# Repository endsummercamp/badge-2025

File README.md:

# badge-2025

Repository containing the schematics for the flex PCB badge distributed at ESC{21}.

The schematics are licensed under the CERN OHL S v2 license.

The badge has been designed by [Jacopo Franco](https://www.jacopofranco.com/), that we thank for the effort in making this literal show of force a reality ;)

Special thanks to [Kezi](https://github.com/Kezii), [Kowalski](https://github.com/kowalski7cc), [K3lite](https://github.com/k3lite) & [Baobots](https://github.com/baobots) for the efforts spent into debugging & flashing all of them during the camp.

And for going the extra mile and designing a custom case that solves many assembly issues, a very felt thanks to [k0bld](https://github.com/k0bld).

<video src="https://github.com/user-attachments/assets/acb0492f-e134-4207-b74a-9145ce9de10b"
       autoplay
       loop
       muted
       playsinline
       width="600">
  Your browser does not support the video tag.
</video>

---

# Badge Instructions

## Assembly

* The badge must be folded into position.
* To keep it fixed, we recommend using **UV glue**, **superglue**, or **thin double-sided tape**.
* **Do not solder directly** onto the PET substrate — this is very challenging, even with bismuth low-temperature solder.

## Flashing
**USB communication is not supported** — the port is for charging only.
To flash the badge the first time, make use of the UART and the power pins as below.

### USB-C Connector

* The USB-C must also be folded.
* Align the tab with the solid line located after the resistors.
* With the **copper contacts facing outward**, insert the connector into a male USB Type-C cable.

---

## Charging
* There are no LEDs to indicate charging progress. The charger is however guaranteed to fully charge the battery in 2.5h. The battery is fully protected and the charger has multiple overcurrent, overvoltage and temperature protections. It can trickle-charge.
* Battery life is approximately 4h with the "All sides music" profile and the WiFi radio at 8.5dBm.
* An **interrupt pin** connected to the charger will change state during charging. You will have to implement it yourself.

---

## Firmware

* The badge ships with the **WLED firmware** by default.
* * Firmware updates can be done via **WLED OTA** or the **Serial pads**.
* To connect:

  1. Connect to the Wi-Fi network:

     ```text
     SSID: wled-ap  
     Password: wled1234
     ```
  2. Open the address in your browser:

     ```text
     4.3.2.1
     ```

---

## Pinout

```text
Charger status:       GPIO 10
Battery voltage:      Analog GPIO 3 (divider only enabled when LED MOSFET is ON)
LEDs MOSFET:          GPIO 4
LED data:             GPIO 8
I²C SDA:              GPIO 7
I²C SCL:              GPIO 6
Touch button 1:       GPIO 0
Touch button 2:       GPIO 1
```

---

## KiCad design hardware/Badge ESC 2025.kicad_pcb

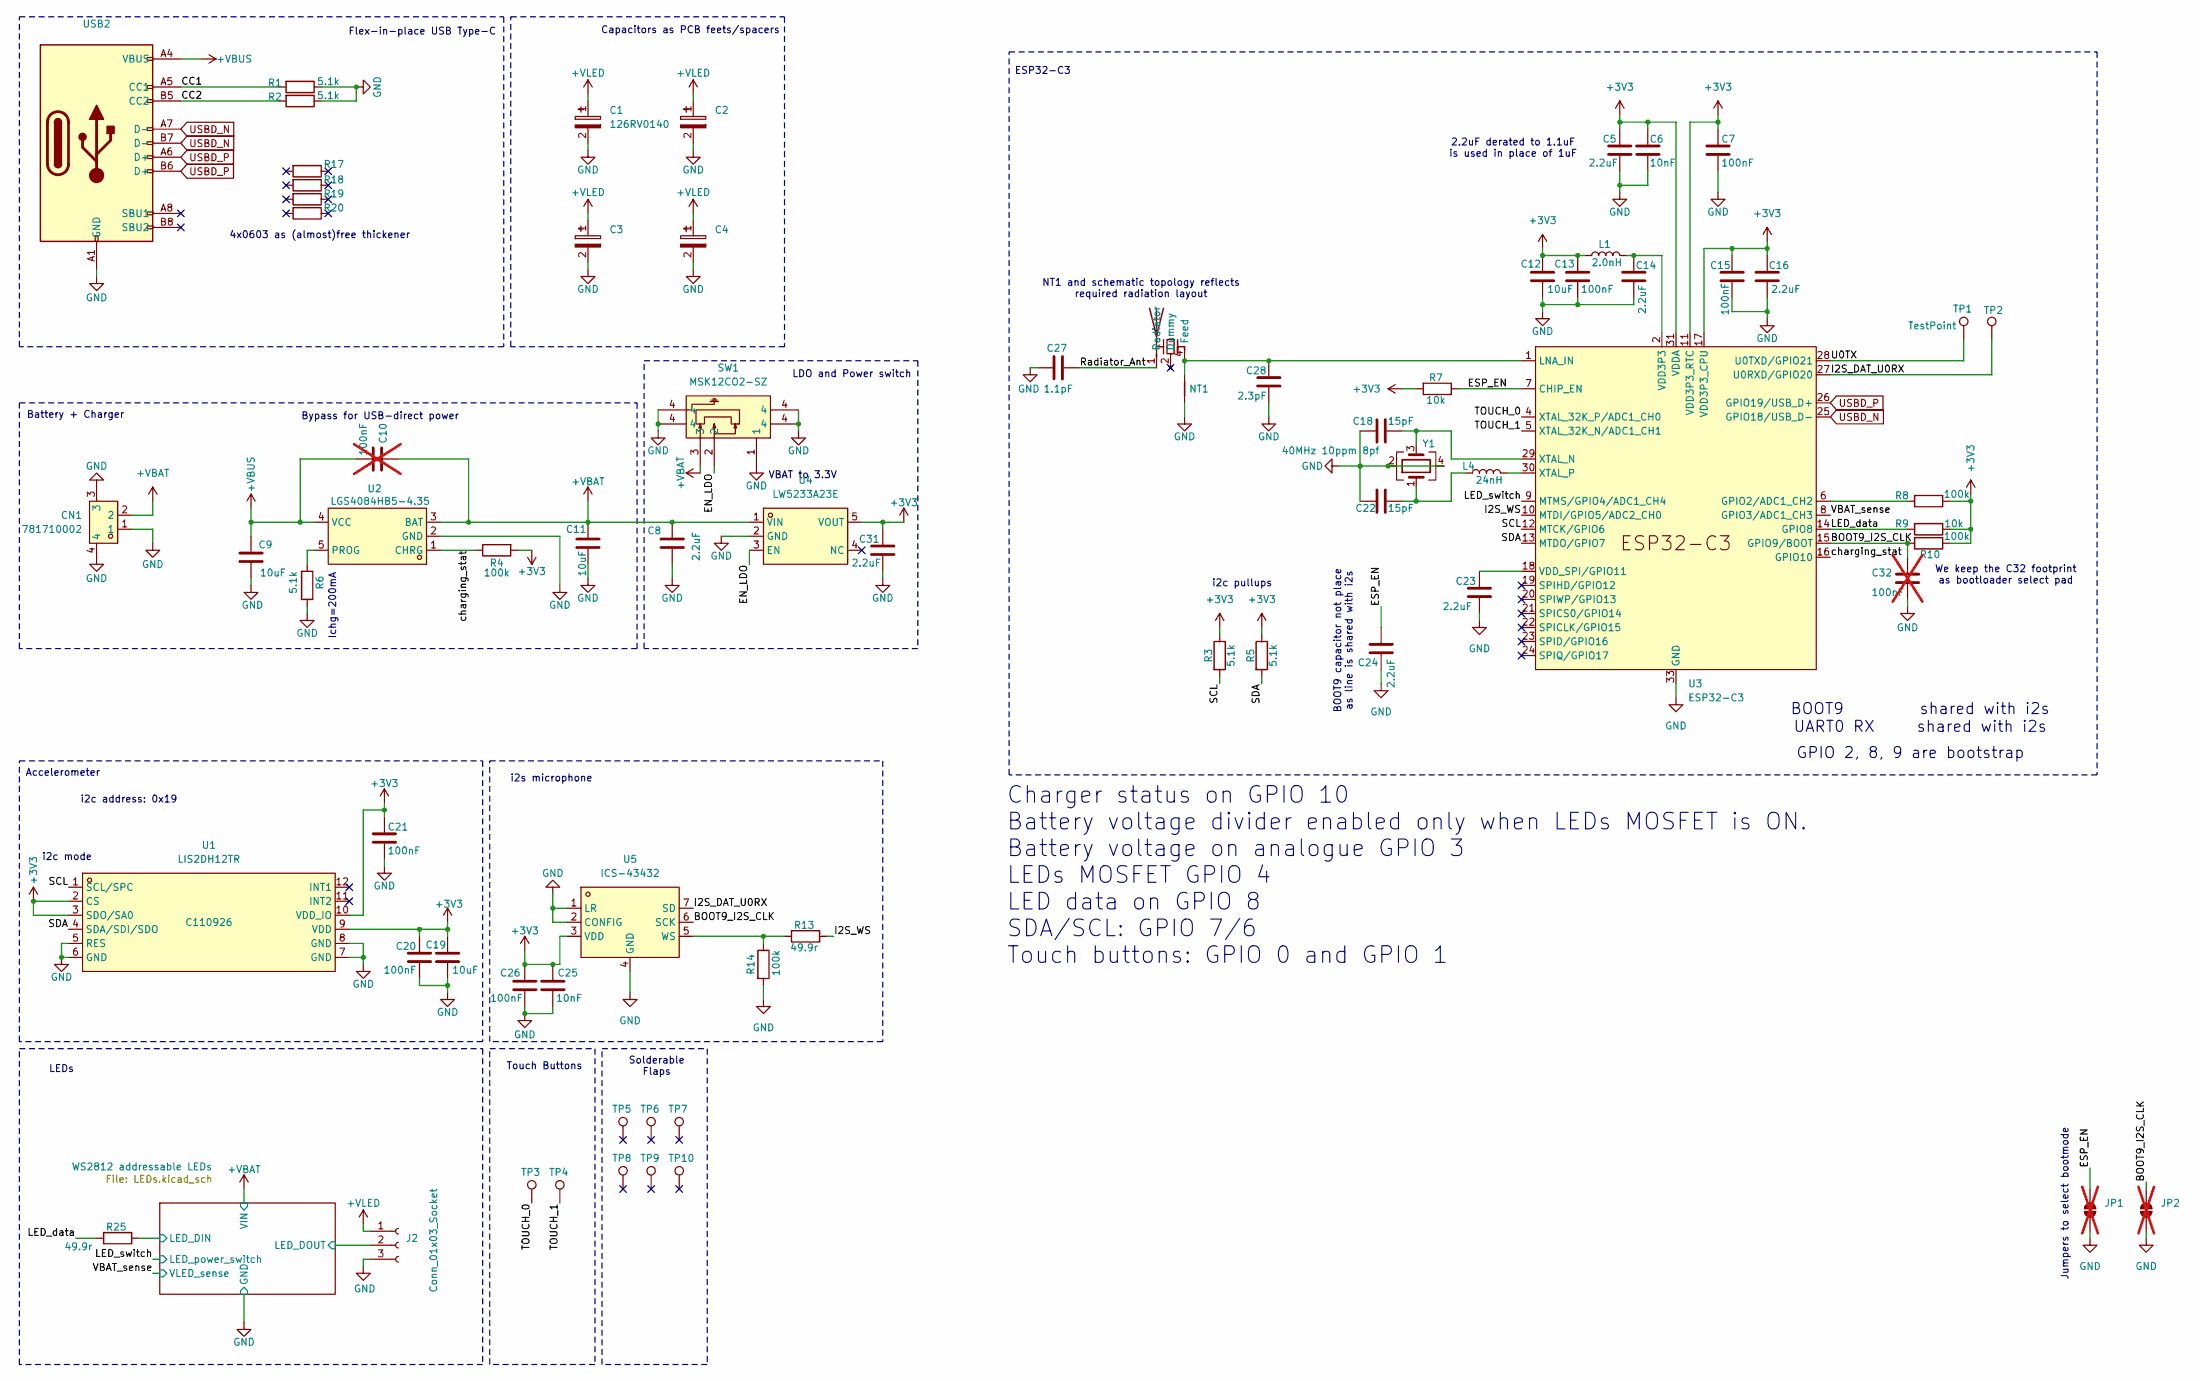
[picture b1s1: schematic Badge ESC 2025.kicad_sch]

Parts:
ANT2: ANT016008LCS2442MA; ANT-SMD_6P-L1.6-W0.8-P1.20-1; LCSC C76585
C1, C2, C3, C4: 126RV0140; CAP-SMD_BD4.0-L4.3-W4.3-LS5.1-FD; LCSC C7461271
C5, C8, C14, C16, C23, C24, C31: 2.2uF; C_0402_1005Metric; LCSC C12530
C6, C25: 10nF; C_0402_1005Metric; LCSC C15195
C7, C13, C15, C20, C21, C26: 100nF; C_0402_1005Metric; LCSC C1525
C9, C11, C12, C19: 10uF; C_0603_1608Metric; LCSC C19702
C10, C32: 100nF; C_0402_1005Metric; LCSC C1525; not fitted
C18, C22: 15pF; C_0402_1005Metric; LCSC C1548
C27: 1.1pF; C_0402_1005Metric; LCSC C88920
C28: 2.3pF; C_0402_1005Metric; LCSC C2190124
CN1: 781710002; CONN-SMD_2P-P1.20_781710002; LCSC Part C505023
J2: Conn_01x03_Socket; SolderJumper-3_P1.3mm_Open_RoundedPad1.0x1.5mm_NumberLabels
JP1, JP2: SolderJumper_2_Open; SolderJumper-2_P1.3mm_Open_Pad0.5x0.5mm; not fitted
L1: 2.0nH; L_0402_1005Metric; LCSC C76769
L4: 24nH; L_0402_1005Metric; LCSC C404641
NT1: NetTie_2; net_tie_2pins_0.2
R1, R2, R3, R5, R6: 5.1k; R_0402_1005Metric; LCSC C25905
R4, R8, R10, R14: 100k; R_0402_1005Metric; LCSC C25741
R7, R9: 10k; R_0402_1005Metric; LCSC C25744
R13, R17, R18, R19, R20, R25: 49.9r; R_0603_1608Metric; LCSC C23185
SW1: MSK12CO2-SZ; SW-TH_MSK12C02; LCSC C2681568
TP1, TP2: TestPoint; TestPoint_Pad_D1.0mm
TP3, TP4: TestPoint; Touch_pad_ESC
TP5, TP6, TP7, TP8, TP9, TP10: Solder_flap; Solder_flap_ESC
U1: LIS2DH12TR; LGA-12_L2.0-W2.0-P0.50-BL; LCSC C110926
U2: LGS4084HB5-4.35; SOT-23-5_L2.9-W1.6-P0.95-LS2.8-TL; LCSC C20618071
U3: ESP32-C3; QFN-32-1EP_5x5mm_P0.5mm_EP3.45x3.45mm; LCSC C2858491
U4: LW5233A23E; SOT-23-5_L3.0-W1.7-P0.95-LS2.8-BR; LCSC Part C20630437
U5: ICS-43432; SENSOR-SMD_ICS-43432; LCSC C574021
USB2: USB_Type_C_FlexPCB_Fold
Y1: 40MHz 10ppm 8pf; Crystal_SMD_2016-4Pin_2.0x1.6mm; LCSC C2835990

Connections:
+3V3: C5.2, C6.1, C7.1, C12.1, C13.1, C15.1, C16.2, C19.1, C20.1, C21.1, C25.2, C26.2, C31.2, L1.1, R3.1, R4.2, R5.1, R7.2, R8.1, R9.1, R10.1, U1.2 (CS), U1.3 (SDO/SA0), U1.9 (VDD), U1.10 (VDD_IO), U3.11 (VDD3P3_RTC), U3.17 (VDD3P3_CPU), U3.31 (VDDA), U3.32 (VDDA), U4.5 (VOUT), U5.3 (VDD)
+VBAT: C8.1, C10.1, C11.1, CN1.2, SW1.3, U2.3 (BAT), U4.1 (VIN); also elsewhere on the board
+VBUS: C9.1, C10.2, U2.4 (VCC), USB2.A4 (VBUS), USB2.A9 (VBUS), USB2.B4 (VBUS), USB2.B9 (VBUS)
+VLED: C1.1, C2.1, C3.1, C4.1, J2.1; also elsewhere on the board
/BOOT9_I2S_CLK: C32.1, JP2.2 (B), R10.2, U3.15 (GPIO9/BOOT), U5.6 (SCK)
/CC1: R1.2, USB2.A5 (CC1)
/CC2: R2.2, USB2.B5 (CC2)
/EN_LDO: SW1.2, U4.3 (EN)
/ESP_EN: C24.2, JP1.2 (B), R7.1, U3.7 (CHIP_EN)
/I2S_DAT_U0RX: TP2.1, U3.27 (U0RXD/GPIO20), U5.7 (SD)
/I2S_WS: R13.1, U3.10 (MTDI/GPIO5/ADC2_CH0)
/LED_data: R9.2, R25.2, U3.14 (GPIO8)
/LED_switch: U3.9 (MTMS/GPIO4/ADC1_CH4); also elsewhere on the board
/Radiator_Ant: ANT2.1 (Radiator), C27.1
/SCL: R3.2, U1.1 (SCL/SPC), U3.12 (MTCK/GPIO6)
/SDA: R5.2, U1.4 (SDA/SDI/SDO), U3.13 (MTDO/GPIO7)
/TOUCH_0: TP3.1, U3.4 (XTAL_32K_P/ADC1_CH0)
/TOUCH_1: TP4.1, U3.5 (XTAL_32K_N/ADC1_CH1)
/U0TX: TP1.1, U3.28 (U0TXD/GPIO21)
/VBAT_sense: U3.8 (GPIO3/ADC1_CH3); also elsewhere on the board
/WS2812 addressable LEDs/LED_DIN: R25.1; also elsewhere on the board
/WS2812 addressable LEDs/LED_DOUT: J2.2; also elsewhere on the board
/charging_stat: R4.1, U2.1 (CHRG), U3.16 (GPIO10)
GND: C1.2, C2.2, C3.2, C4.2, C5.1, C6.2, C7.2, C8.2, C9.2, C11.2, C12.2, C13.2, C14.2, C15.2, C16.1, C18.1, C19.2, C20.2, C21.2, C22.1, C23.1, C24.1, C25.1, C26.1, C27.2, C28.1, C31.1, C32.2, CN1.1, CN1.3, CN1.4, J2.3, JP1.1 (A), JP2.1 (A), NT1.1, R1.1, R2.1, R6.1, R14.2, SW1.1, SW1.4, U1.5 (RES), U1.6 (GND), U1.7 (GND), U1.8 (GND), U2.2 (GND), U3.33 (GND), U4.2 (GND), U5.1 (LR), U5.2 (CONFIG), U5.4 (GND), USB2.A1 (GND), USB2.A12 (GND), USB2.B1 (GND), USB2.B12 (GND), Y1.2, Y1.4; also elsewhere on the board
unnamed: ANT2.4 (Feed), C28.2, NT1.2, U3.1 (LNA_IN)
unnamed: C14.1, L1.2, U3.2 (VDD3P3), U3.3 (VDD3P3)
unnamed: C22.2, L4.1, Y1.1
unnamed: R6.2, U2.5 (PROG)
unnamed: R8.2, U3.6 (GPIO2/ADC1_CH2)
unnamed: C23.2, U3.18 (VDD_SPI/GPIO11)
unnamed: C18.2, U3.29 (XTAL_N), Y1.3
unnamed: L4.2, U3.30 (XTAL_P)
unnamed: R13.2, R14.1, U5.5 (WS)
USBD_N: U3.25 (GPIO18/USB_D-), USB2.A7 (D-), USB2.B7 (D-)
USBD_P: U3.26 (GPIO19/USB_D+), USB2.A6 (D+), USB2.B6 (D+)

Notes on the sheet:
LEDs
4x0603 as (almost)free thickener
Bypass for USB-direct power
Solderable Flaps
NT1 and schematic topology reflects required radiation layout
Jumpers to select bootmode
Capacitors as PCB feets/spacers
i2c pullups
BOOT9 shared with i2s UART0 RX shared with i2s
Flex-in-place USB Type-C
Touch Buttons
Charger status on GPIO 10 Battery voltage divider enabled only when LEDs MOSFET is ON. Battery voltage on analogue GPIO 3 LEDs MOSFET GPIO 4 LED data on GPIO 8 SDA/SCL: GPIO 7/6 Touch buttons: GPIO 0 and GPIO 1
i2c address: 0x19
VBAT to 3.3V
Accelerometer
LDO and Power switch
We keep the C32 footprint as bootloader select pad
BOOT9 capacitor not place as line is shared with i2s
ESP32-C3
2.2uF derated to 1.1uF is used in place of 1uF
GPIO 2, 8, 9 are bootstrap
Ichg=200mA
i2s microphone
Battery + Charger
i2c mode

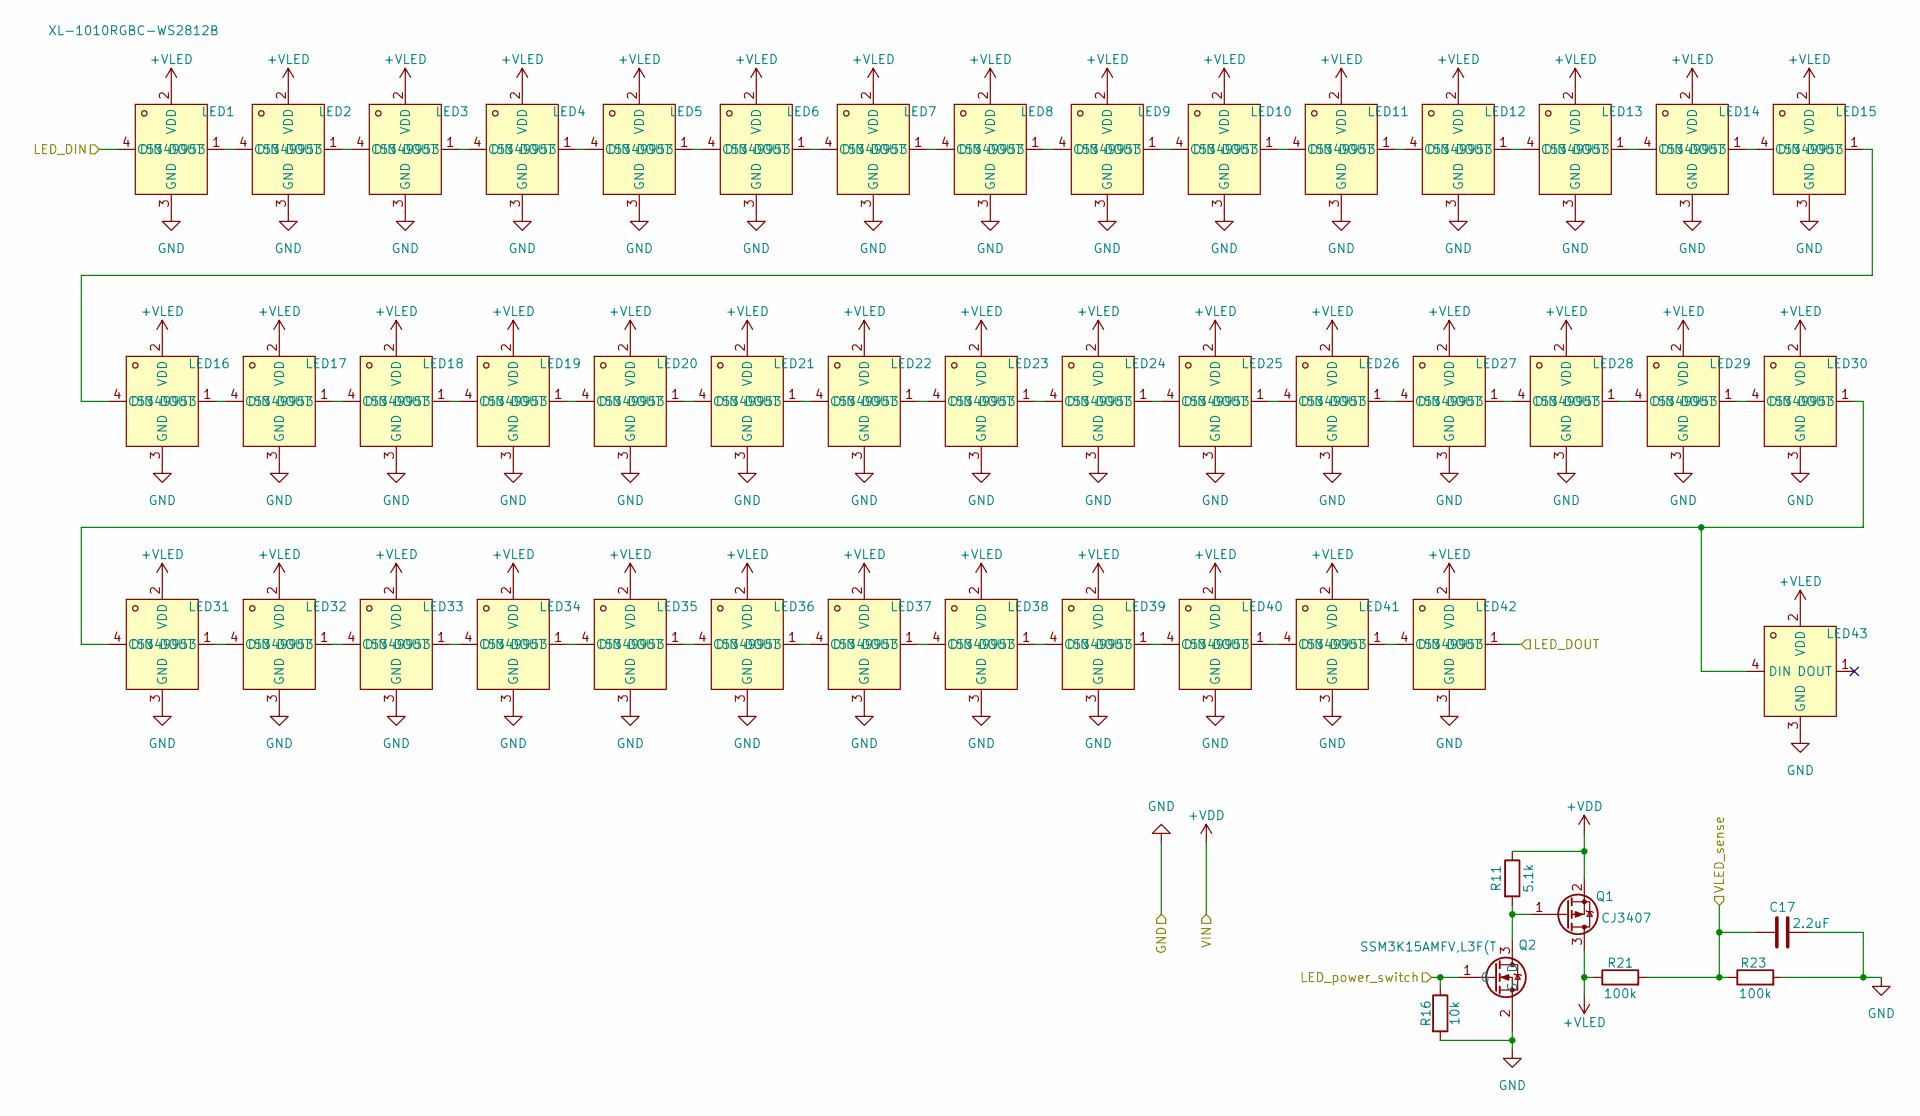
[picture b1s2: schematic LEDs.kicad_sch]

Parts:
C17: 2.2uF; C_0402_1005Metric; LCSC C12530
LED1, LED2, LED3, LED4, LED5, LED6, LED7, LED8, LED9, LED10, LED11, LED12, LED13, LED14, LED15, LED16, LED17, LED18, LED19, LED20, LED21, LED22, LED23, LED24, LED25, LED26, LED27, LED28, LED29, LED30, LED31, LED32, LED33, LED34, LED35, LED36, LED37, LED38, LED39, LED40, LED41, LED42, LED43: XL-1010RGBC-WS2812B; LED-SMD_4P-L1.0-W1.0-TL_XL-1010RGBC-WS2812B; LCSC C5349953
Q1: CJ3407; SOT-23; LCSC C15903
Q2: SSM3K15AMFV,L3F(T; SOT-723; LCSC C516857
R11: 5.1k; R_0402_1005Metric; LCSC C25905
R16: 10k; R_0402_1005Metric; LCSC C25744
R21, R23: 100k; R_0402_1005Metric; LCSC C25741

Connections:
+VBAT: Q1.2 (S), R11.1; also elsewhere on the board
+VLED: LED1.2 (VDD), LED2.2 (VDD), LED3.2 (VDD), LED4.2 (VDD), LED5.2 (VDD), LED6.2 (VDD), LED7.2 (VDD), LED8.2 (VDD), LED9.2 (VDD), LED10.2 (VDD), LED11.2 (VDD), LED12.2 (VDD), LED13.2 (VDD), LED14.2 (VDD), LED15.2 (VDD), LED16.2 (VDD), LED17.2 (VDD), LED18.2 (VDD), LED19.2 (VDD), LED20.2 (VDD), LED21.2 (VDD), LED22.2 (VDD), LED23.2 (VDD), LED24.2 (VDD), LED25.2 (VDD), LED26.2 (VDD), LED27.2 (VDD), LED28.2 (VDD), LED29.2 (VDD), LED30.2 (VDD), LED31.2 (VDD), LED32.2 (VDD), LED33.2 (VDD), LED34.2 (VDD), LED35.2 (VDD), LED36.2 (VDD), LED37.2 (VDD), LED38.2 (VDD), LED39.2 (VDD), LED40.2 (VDD), LED41.2 (VDD), LED42.2 (VDD), LED43.2 (VDD), Q1.3 (D), R21.1; also elsewhere on the board
/LED_switch: Q2.1 (G), R16.1; also elsewhere on the board
/VBAT_sense: C17.2, R21.2, R23.1; also elsewhere on the board
/WS2812 addressable LEDs/LED_DIN: LED1.4 (DIN); also elsewhere on the board
/WS2812 addressable LEDs/LED_DOUT: LED42.1 (DOUT); also elsewhere on the board
GND: C17.1, LED1.3 (GND), LED2.3 (GND), LED3.3 (GND), LED4.3 (GND), LED5.3 (GND), LED6.3 (GND), LED7.3 (GND), LED8.3 (GND), LED9.3 (GND), LED10.3 (GND), LED11.3 (GND), LED12.3 (GND), LED13.3 (GND), LED14.3 (GND), LED15.3 (GND), LED16.3 (GND), LED17.3 (GND), LED18.3 (GND), LED19.3 (GND), LED20.3 (GND), LED21.3 (GND), LED22.3 (GND), LED23.3 (GND), LED24.3 (GND), LED25.3 (GND), LED26.3 (GND), LED27.3 (GND), LED28.3 (GND), LED29.3 (GND), LED30.3 (GND), LED31.3 (GND), LED32.3 (GND), LED33.3 (GND), LED34.3 (GND), LED35.3 (GND), LED36.3 (GND), LED37.3 (GND), LED38.3 (GND), LED39.3 (GND), LED40.3 (GND), LED41.3 (GND), LED42.3 (GND), LED43.3 (GND), Q2.2 (S), R16.2, R23.2; also elsewhere on the board
unnamed: LED1.1 (DOUT), LED2.4 (DIN)
unnamed: LED2.1 (DOUT), LED3.4 (DIN)
unnamed: LED3.1 (DOUT), LED4.4 (DIN)
unnamed: LED4.1 (DOUT), LED5.4 (DIN)
unnamed: LED5.1 (DOUT), LED6.4 (DIN)
unnamed: LED6.1 (DOUT), LED7.4 (DIN)
unnamed: LED7.1 (DOUT), LED8.4 (DIN)
unnamed: LED8.1 (DOUT), LED9.4 (DIN)
unnamed: LED9.1 (DOUT), LED10.4 (DIN)
unnamed: LED10.1 (DOUT), LED11.4 (DIN)
unnamed: LED11.1 (DOUT), LED12.4 (DIN)
unnamed: LED12.1 (DOUT), LED13.4 (DIN)
unnamed: LED13.1 (DOUT), LED14.4 (DIN)
unnamed: LED14.1 (DOUT), LED15.4 (DIN)
unnamed: LED15.1 (DOUT), LED16.4 (DIN)
unnamed: LED16.1 (DOUT), LED17.4 (DIN)
unnamed: LED17.1 (DOUT), LED18.4 (DIN)
unnamed: LED18.1 (DOUT), LED19.4 (DIN)
unnamed: LED19.1 (DOUT), LED20.4 (DIN)
unnamed: LED20.1 (DOUT), LED21.4 (DIN)
unnamed: LED21.1 (DOUT), LED22.4 (DIN)
unnamed: LED22.1 (DOUT), LED23.4 (DIN)
unnamed: LED23.1 (DOUT), LED24.4 (DIN)
unnamed: LED24.1 (DOUT), LED25.4 (DIN)
unnamed: LED25.1 (DOUT), LED26.4 (DIN)
unnamed: LED26.1 (DOUT), LED27.4 (DIN)
unnamed: LED27.1 (DOUT), LED28.4 (DIN)
unnamed: LED28.1 (DOUT), LED29.4 (DIN)
unnamed: LED29.1 (DOUT), LED30.4 (DIN)
unnamed: LED30.1 (DOUT), LED31.4 (DIN), LED43.4 (DIN)
unnamed: LED31.1 (DOUT), LED32.4 (DIN)
unnamed: LED32.1 (DOUT), LED33.4 (DIN)
unnamed: LED33.1 (DOUT), LED34.4 (DIN)
unnamed: LED34.1 (DOUT), LED35.4 (DIN)
unnamed: LED35.1 (DOUT), LED36.4 (DIN)
unnamed: LED36.1 (DOUT), LED37.4 (DIN)
unnamed: LED37.1 (DOUT), LED38.4 (DIN)
unnamed: LED38.1 (DOUT), LED39.4 (DIN)
unnamed: LED39.1 (DOUT), LED40.4 (DIN)
unnamed: LED40.1 (DOUT), LED41.4 (DIN)
unnamed: LED41.1 (DOUT), LED42.4 (DIN)
unnamed: Q1.1 (G), Q2.3 (D), R11.2

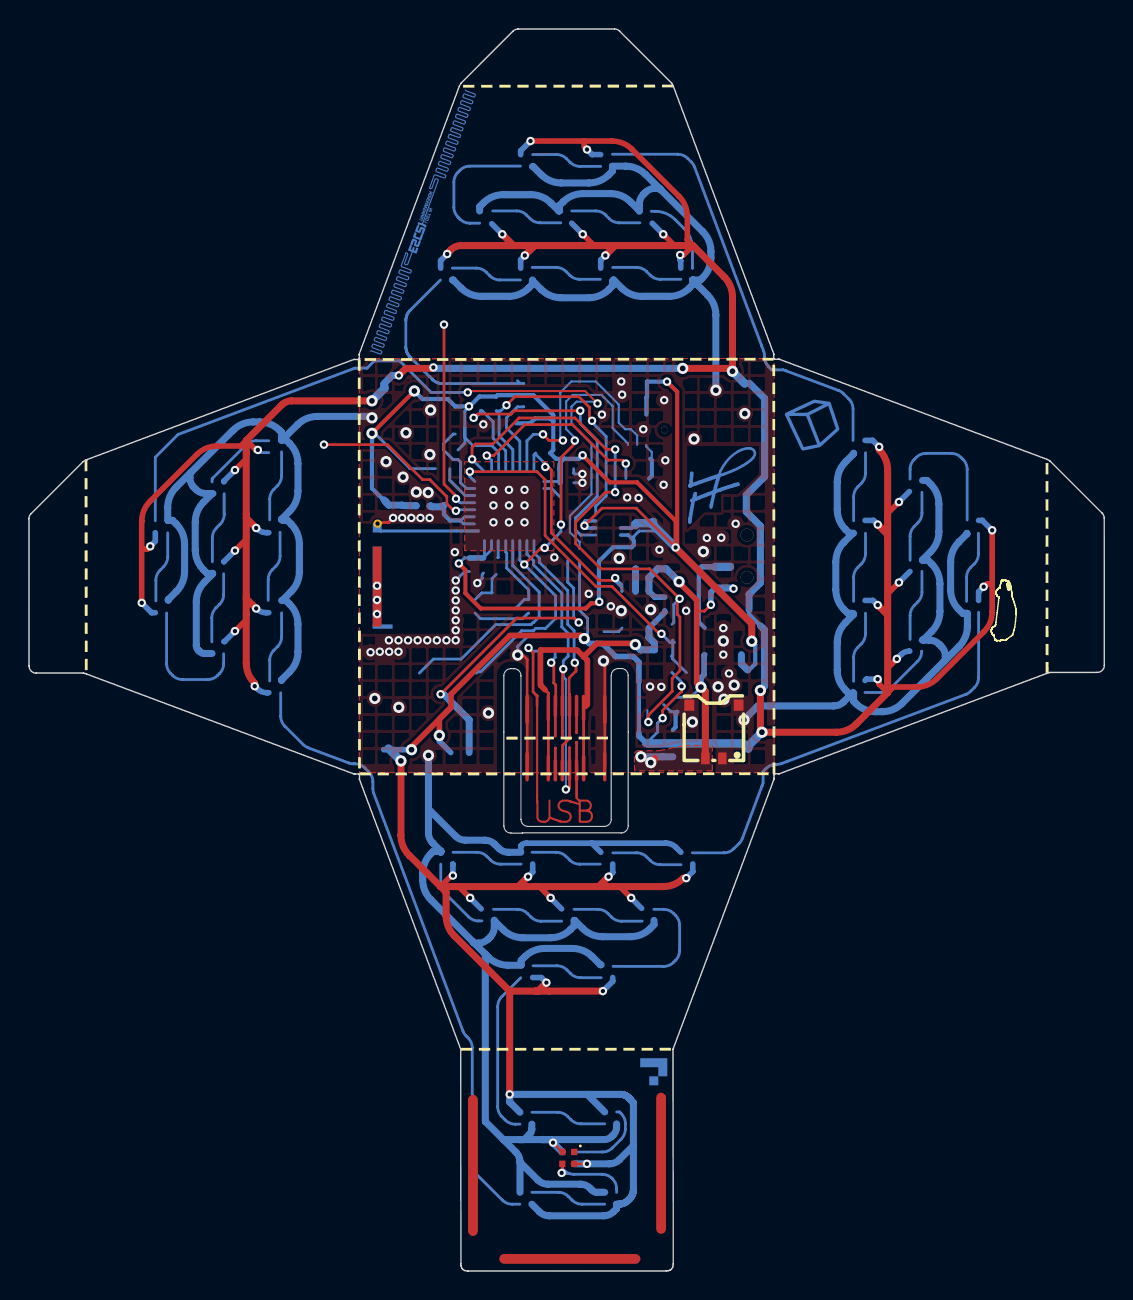
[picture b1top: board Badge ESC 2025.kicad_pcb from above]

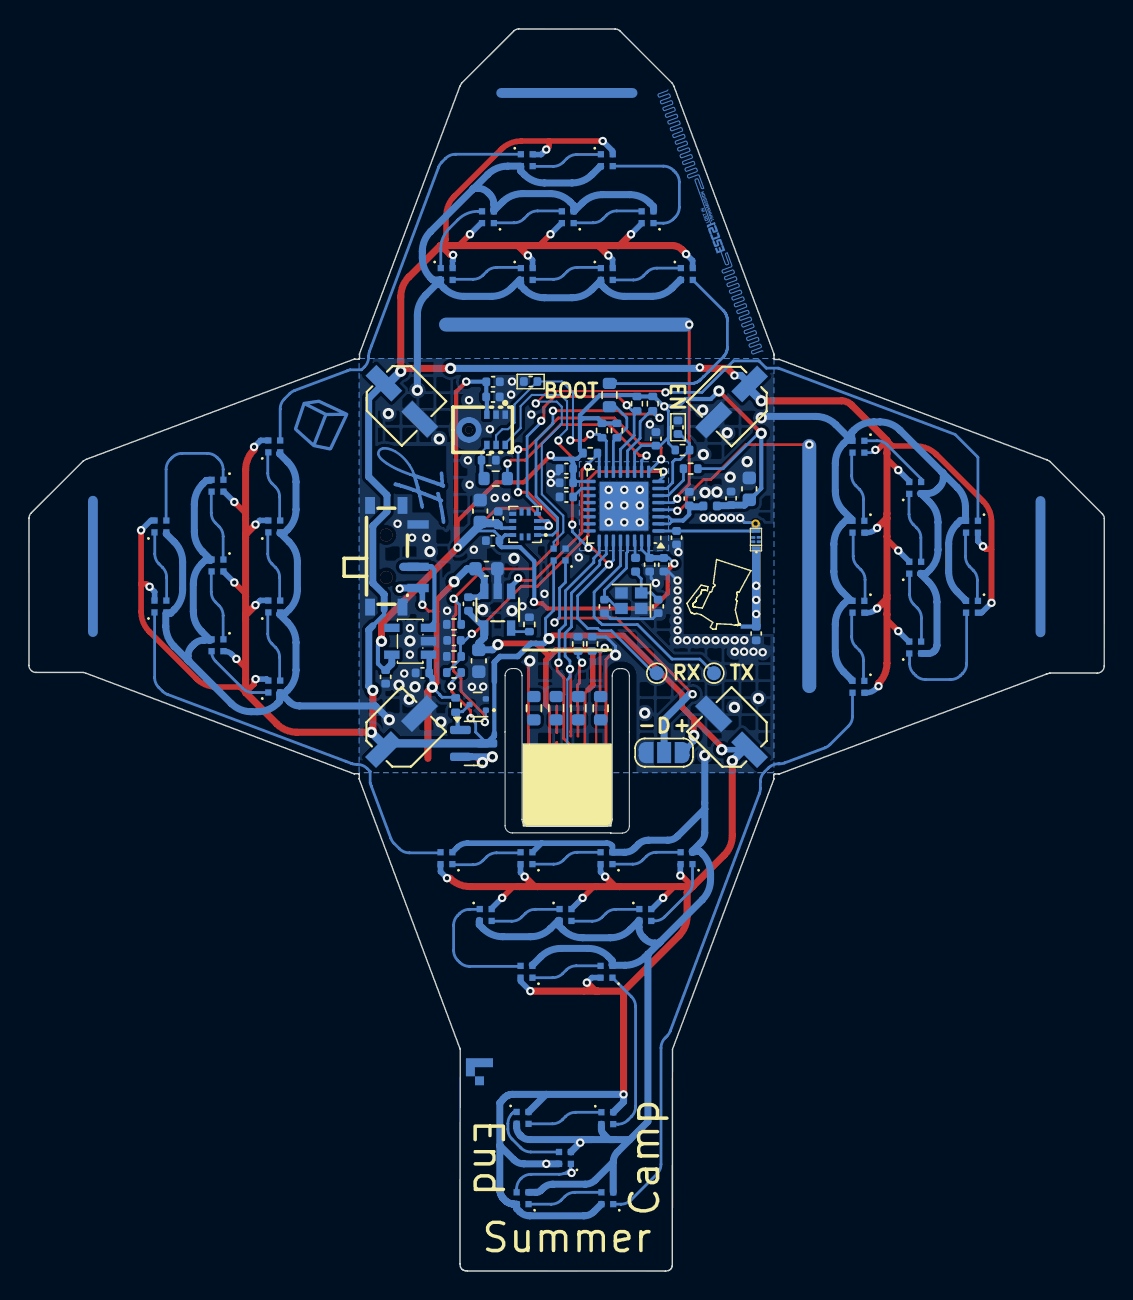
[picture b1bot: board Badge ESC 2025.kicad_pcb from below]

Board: 2 copper layers, 76.1 x 87.9 mm, 120 parts (113 on the bottom side), 77 nets.

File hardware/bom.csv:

Designator,Footprint,Quantity,Value,LCSC Part #
ANT2,ANT-SMD_6P-L1.6-W0.8-P1.20-1,1,ANT016008LCS2442MA,C76585
"C1, C2, C3, C4",CAP-SMD_BD4.0-L4.3-W4.3-LS5.1-FD,4,126RV0140,
"C11, C12, C19, C9",0603,4,10uF,
"C13, C15, C20, C21, C7",0402,5,100nF,
"C14, C16, C23, C24, C31, C5, C8",0402,7,2.2uF,
C17,0402,1,2.2uF,C12530
"C18, C22",0402,2,15pF,C1548
C25,0402,1,10nF,C15195
C26,0402,1,100nF,C1525
C27,0402,1,1.1pF,C88920
C28,0402,1,2.3pF,C2190124
C6,0402,1,10nF,
CN1,CONN-SMD_2P-P1.20_781710002,1,781710002,C505023
L1,0402,1,2.0nH,C76769
L4,0402,1,24nH,C404641
"LED1, LED10, LED11, LED12, LED13, LED14, LED15, LED16, LED17, LED18, LED19, LED2, LED20, LED21, LED22, LED23, LED24, LED25, LED26, LED27, LED28, LED29, LED3, LED30, LED31, LED32, LED33, LED34, LED35, LED36, LED37, LED38, LED39, LED4, LED40, LED41, LED42, LED43, LED5, LED6, LED7, LED8, LED9",LED-SMD_4P-L1.0-W1.0-TL_XL-1010RGBC-WS2812B,43,XL-1010RGBC-WS2812B,
Q1,SOT-23,1,CJ3407,C15903
Q2,SOT-723,1,"SSM3K15AMFV,L3F(T",
"R1, R11, R2, R3, R5, R6",0402,6,5.1k,C25905
"R10, R14, R21, R23, R4, R8",0402,6,100k,C25741
"R13, R17, R18, R19, R20, R25",0603,6,49.9r,C23185
"R16, R7, R9",0402,3,10k,C25744
SW1,SW-TH_MSK12C02,1,MSK12CO2-SZ,
U1,LGA-12_L2.0-W2.0-P0.50-BL,1,LIS2DH12TR,
U2,SOT-23-5_L2.9-W1.6-P0.95-LS2.8-TL,1,LGS4084HB5-4.35,C20618071
U3,QFN-32-1EP_5x5mm_P0.5mm_EP3.45x3.45mm,1,ESP32-C3,C2858491
U4,SOT-23-5_L3.0-W1.7-P0.95-LS2.8-BR,1,LW5233A23E,C20630437
U5,SENSOR-SMD_ICS-43432,1,ICS-43432,C574021
Y1,Crystal_SMD_2016-4Pin_2.0x1.6mm,1,40MHz 10ppm 8pf,C2835990

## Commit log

2025-09-10 fix readme
2025-09-10 BOM + positions
2025-09-10 add gerbers
2025-09-11 added video
2025-09-11 looping video
2025-09-15 Add K3lite to special thanks
2025-09-16 3d printable badge case
2025-09-19 added instructions
2025-10-27 Add README for flashing WLED firmware on BadgESC{21}
    Added instructions for flashing and configuring WLED firmware for BadgESC{21}, including steps for connecting to the access point and uploading configuration files.
2025-10-27 compiled WLED from branch Nightly Release 20251027
2025-10-27 Enhance README with recompilation instructions
    Added detailed instructions for recompiling the firmware.
2025-10-27 add compiler configuration
2025-10-27 Rename firmware/firmware.bin to firmware/legacy/v1_esc{21}_supplied_wled.bin
2025-10-27 legacy firmware changed naming
2025-10-27 Update README with flashing instructions
    Added instructions for flashing the firmware using esptool.
2025-10-28 Update README with battery life details
    Added information about battery life with WiFi settings.
2025-10-28 Updated presets
    Added a new preset with segments enabled and different music effects for the sides and top.
2025-10-28 Add README with folding instructions for BadgESC{21} Badge
    Added detailed folding instructions for the BadgESC{21} Badge, including steps for initial positioning, power switch testing, and final assembly.
2025-10-28 Add acknowledgment for k0bld's custom case design
    Added a thank you note for k0bld for designing a custom case.
2025-10-28 Fix markdown
2025-10-28 Revised wled connection IP
    Updated instructions for device connection and navigation.
2025-10-28 Update Access Point name in README
2026-05-16 Updated firmware and compilation config
